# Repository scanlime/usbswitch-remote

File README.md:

# usbswitch-remote

Replacement firmware and optional wired remote for UGREEN brand USB 2.0 sharing switch.

I've tested this on a version of the switch from 2017 which had five USB type A sockets,
and the button was in one corner. Newer versions of the same product appear to have
four Type B and one Type A, which no longer violates the USB spec, and the button is
in the center. I'm not sure if those units use compatible firmware.

This device is effectively a high-speed analog multiplexer, based on a tree of
three [SV7030 USB 2.0 switch](http://product.savitech-ic.com/DataSheet/SV7030DS-REV095a.pdf)
chips controlled by an [STM8S003F3 microcontroller](https://www.st.com/resource/en/datasheet/stm8s003k3.pdf).

## Firmware

The STM8 is a low-cost 8-bit micro with 8kB of flash memory, and there's an available PCB footprint
for an STLink or compatible debug interface.

There is no GCC or LLVM port, but we can tolerate [SDCC](http://sdcc.sourceforge.net/) for a small project like this!

The included firmware is written in C for the bare metal, no vendor libraries are needed.
It supports switching channels using the built-in button or an optional wired remote.
The original firmware had quite bad button debouncing, which is fixed. I've also omitted
support for automatic switching with voltage sensing. It could be added, but I didn't want
the feature as I found it distracting.

* Build the firmware with [SDCC](http://sdcc.sourceforge.net/) (optional).
* Install it with either [OpenOCD](http://openocd.org/) or [stm8flash](https://github.com/vdudouyt/stm8flash)

## Remote

To have direct control over switching to each of the four channels, a simple wired
remote with four lighted buttons can be added using an audio cable and some passive
components. See the included schematic. It uses a variant of charlieplexing that drives
four LEDs as usual, then splits the two remaining currents paths into two buttons each,
using an RC circuit to disambiguate them. If this needs a name, I'm calling it Tucoplexing
after my cat Tuco! 😸

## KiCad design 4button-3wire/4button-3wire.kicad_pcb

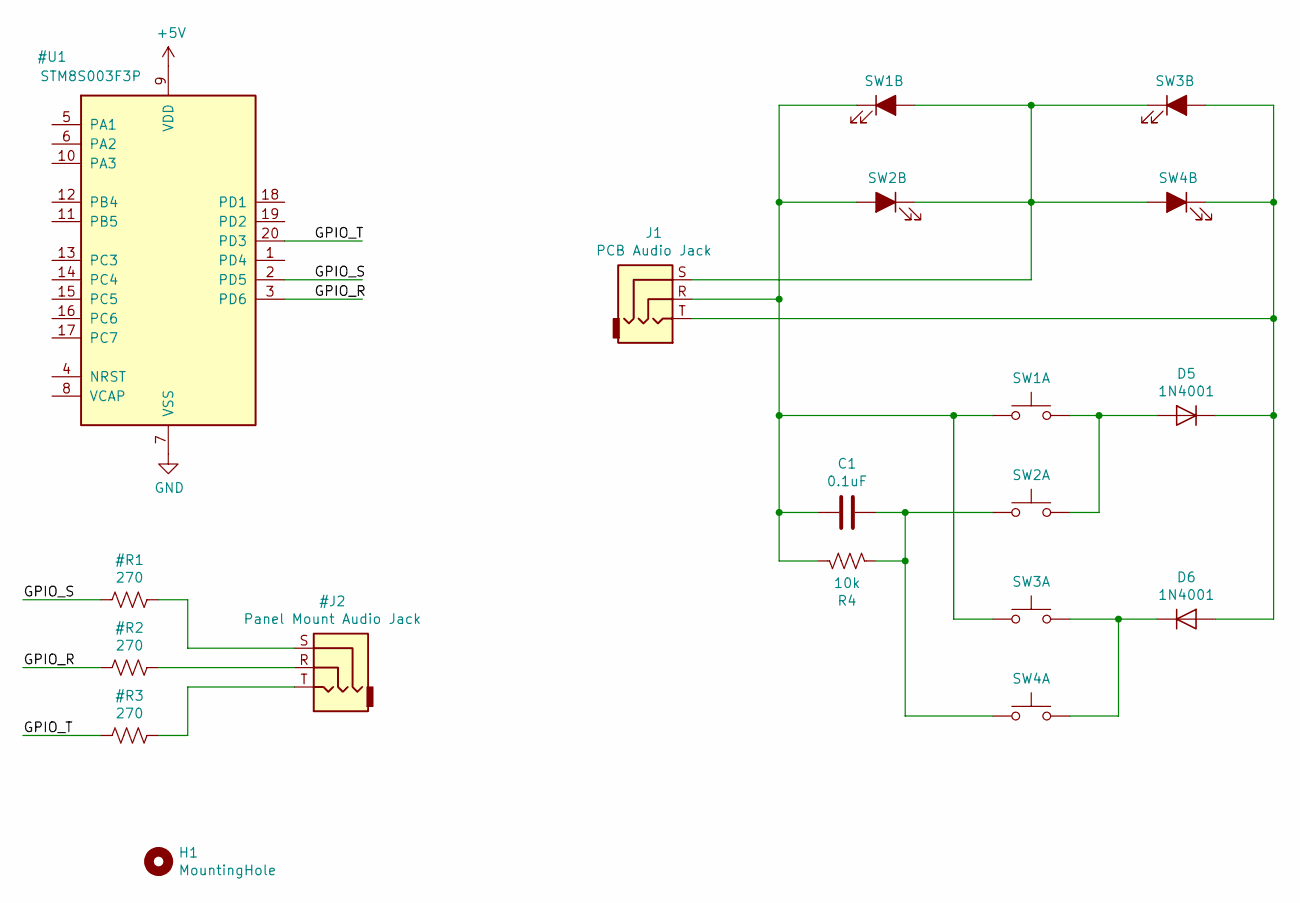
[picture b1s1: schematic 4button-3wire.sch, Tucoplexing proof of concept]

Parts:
C1: 0.1uF; C_Disc_D4.7mm_W2.5mm_P5.00mm
D5, D6: 1N4001; D_DO-35_SOD27_P7.62mm_Horizontal
H1: MountingHole; MountingHole_3.2mm_M3
J1: PCB Audio Jack; Jack_3.5mm_7mmSpacing
R4: 10k; R_Axial_DIN0207_L6.3mm_D2.5mm_P10.16mm_Horizontal
SW1, SW2, SW3, SW4: SW_Push_LED_Separate; SW_LightedPush_ITW_Series39_SmallPads

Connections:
unnamed: C1.1, R4.1, SW2.2, SW4.2
unnamed: C1.2, J1.R, R4.2, SW1.1, SW1.3 (K), SW2.4 (A), SW3.2
unnamed: D5.1 (K), D6.2 (A), J1.T, SW3.4 (A), SW4.3 (K)
unnamed: D5.2 (A), SW1.2, SW2.1
unnamed: D6.1 (K), SW3.1, SW4.1
unnamed: J1.S, SW1.4 (A), SW2.3 (K), SW3.3 (K), SW4.4 (A)

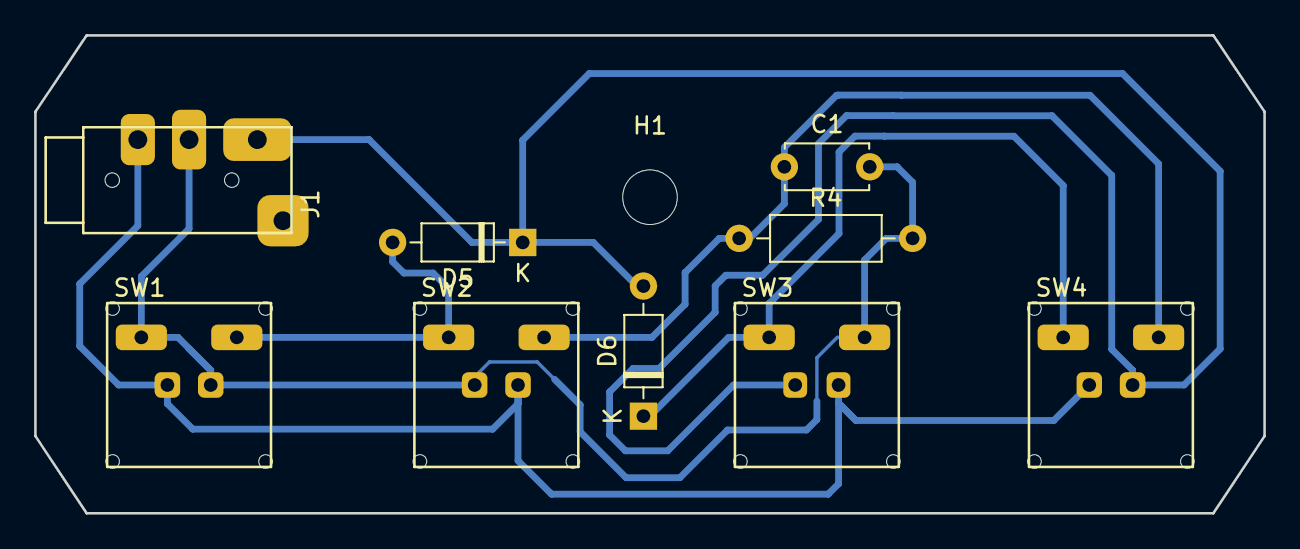
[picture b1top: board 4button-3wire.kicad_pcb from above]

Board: 2 copper layers, 72.0 x 28.0 mm, 10 parts (0 on the bottom side), 6 nets.

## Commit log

2019-02-11 Initial working version
2019-02-11 Tool links
2019-02-11 gitignore
2019-02-11 Include built firmware why not
2019-02-11 quietness
2019-02-11 Include schematic PDF
2019-02-11 Update title block
2019-02-11 Tidy
2019-02-11 Share the RC circuit between both button pairs
2019-02-12 Mostly routed
2019-02-12 Trying to make single layer
    Moved some components around
    Made switch pads a little smaller
    Moved top board edge up
2019-02-12 Changed Switch Footprint
    Made a new footprint with smaller size pads
2019-02-12 Modified Rules to Add Last Trace
    Changed the design rules to allow the last trace to be routed which will require the 1/64" mill bit to be used.
    Could use some cleaning up still.
2019-02-13 First milled PCB revision
2019-02-13 SVG plot
2019-02-13 Move Bottom Board Edge Down 1.5mm
    A little cleanup to reduce the amount of small spaces.
    Closed board outline but not pretty
    Moved traces down to open spacing
2019-02-17 Mechanical prototype
